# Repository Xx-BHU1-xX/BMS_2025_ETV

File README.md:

## Project archive for the 2025 ETV BMS
- Refer to the `hardware` section for design choices and PCB files.
- Refer to the `software` section for firmware dev.

## Yet to be implemented:
- Charging control and charger CAN comms
	- Control charging current and voltage according to INR1650 charge specs
	- J1939 CAN implementation for commanding charging current and voltage 
	- Should be relatively straightforard to implement with new task
- Inital SOH estimation
	- Detailed in the task description for `TaskUpdateSOC` 
- DCIR history
	- Store DCIR values in EEPROM for recovery in the next power cycle

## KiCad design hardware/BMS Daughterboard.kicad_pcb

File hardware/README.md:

# Battery Management System (BMS)

---

## Architecture evolution

### Earlier version
- Used **LTC6804-based slave boards (DC1894B)** with a **Linduino (DC2026)** as the isoSPI master.
- The entire system ran on the **ATmega328P** on the DC2026.
- SRAM was very limited (~2 KB), which was barely enough for:
  - 72× cell voltages, SOC, DCIR values
  - filtering / fault flags
- This became the main bottleneck as features were added.

---

### Revised architecture
- High-level processing was offloaded to an **ESP32**.
- The **DC2026** was retained only for reliable LTC6804 isoSPI communication.
- Direct isoSPI from the ESP32 was avoided to keep hardware and isolation simpler (and to avoid porting the LTC sketchbook :)

---

## Communication and isolation
- **ESP32** is referenced to **GLV**.
- **Linduino (DC2026)** is referenced to **TS**.
- Communication between the two is via an **isolated UART**.

---

## Additional features
- CAN communication for vehicle integration.
- Redundant isolated current sensing:
  - Hall-effect sensor (HBO300 fully differential)
  - Shunt-based sensor (VAT4300 wireless)

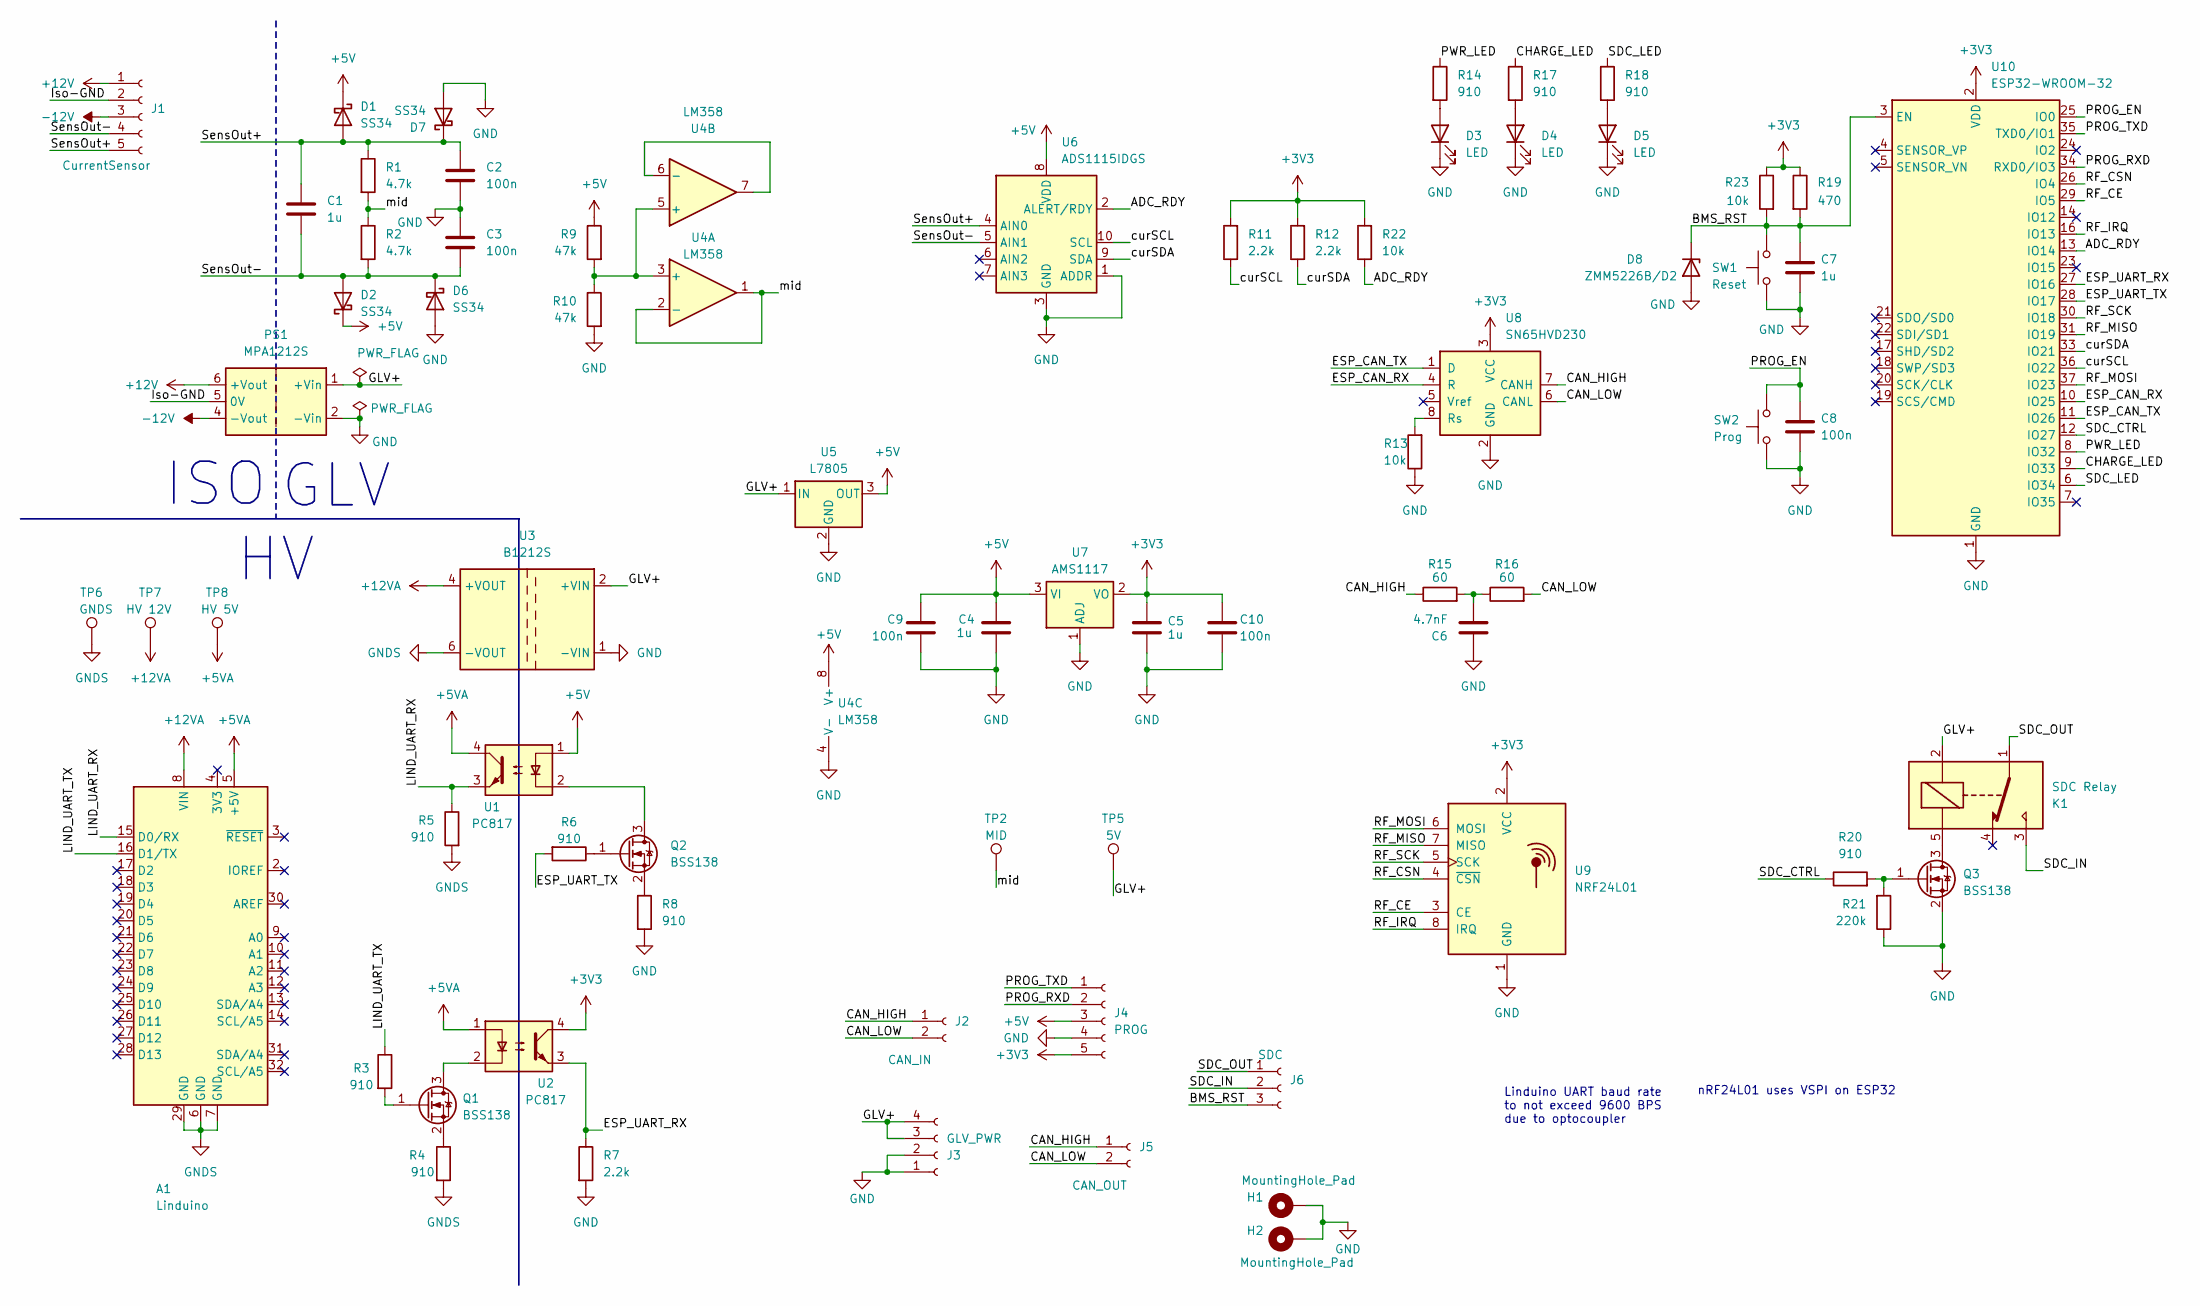
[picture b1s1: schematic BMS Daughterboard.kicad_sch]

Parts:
A1: Linduino
C1, C4, C5, C7: 1u; C_0805_2012Metric_Pad1.18x1.45mm_HandSolder
C2, C3, C8, C9, C10: 100n; C_0805_2012Metric_Pad1.18x1.45mm_HandSolder
C6: 4.7nF; C_0805_2012Metric_Pad1.18x1.45mm_HandSolder
D1, D2, D6, D7: SS34; D_SMC
D3, D4, D5: LED; LED_0805_2012Metric_Pad1.15x1.40mm_HandSolder
D8: ZMM5226B/D2; D_MiniMELF
H1, H2: MountingHole_Pad; MountingHole_3.2mm_M3_DIN965_Pad
J1: CurrentSensor; JST_PH_S5B-PH-K_1x05_P2.00mm_Horizontal
J2: CAN_IN; JST_PH_S2B-PH-K_1x02_P2.00mm_Horizontal
J3: GLV_PWR; JST_PH_S4B-PH-K_1x04_P2.00mm_Horizontal
J4: PROG; PinSocket_1x05_P2.54mm_Vertical
J5: CAN_OUT; JST_PH_S2B-PH-K_1x02_P2.00mm_Horizontal
J6: SDC; JST_PH_S3B-PH-K_1x03_P2.00mm_Horizontal
K1: SDC Relay; Relay_SPDT_SANYOU_SRD_Series_Form_C
PS1: MPA1212S; Converter_DCDC_XP_POWER-IAxxxxS_THT
Q1, Q2, Q3: BSS138
R1, R2: 4.7k; R_0805_2012Metric_Pad1.20x1.40mm_HandSolder
R3, R4, R5, R6, R8, R14, R17, R18, R20: 910; R_0805_2012Metric_Pad1.20x1.40mm_HandSolder
R7, R11, R12: 2.2k; R_0805_2012Metric_Pad1.20x1.40mm_HandSolder
R9, R10: 47k; R_0805_2012Metric_Pad1.20x1.40mm_HandSolder
R13, R22, R23: 10k; R_0805_2012Metric_Pad1.20x1.40mm_HandSolder
R15, R16: 60; R_0805_2012Metric_Pad1.20x1.40mm_HandSolder
R19: 470; R_0805_2012Metric_Pad1.20x1.40mm_HandSolder
R21: 220k; R_0805_2012Metric_Pad1.20x1.40mm_HandSolder
SW1: Reset; Push Button
SW2: Prog; Push Button
TP2: MID; TestPoint_Pad_D1.5mm
TP5: 5V; TestPoint_THTPad_D1.5mm_Drill0.7mm
TP6: GNDS; TestPoint_THTPad_D1.5mm_Drill0.7mm
TP7: HV 12V; TestPoint_THTPad_D1.5mm_Drill0.7mm
TP8: HV 5V; TestPoint_THTPad_D1.5mm_Drill0.7mm
U1, U2: PC817
U3: B1212S; DCDC B1212S
U4: LM358; SOIC-8_3.9x4.9mm_P1.27mm
U5: L7805; TO-252-2
U6: ADS1115IDGS; VSSOP-10_3x3mm_P0.5mm
U7: AMS1117; SOT-223-3_TabPin2
U8: SN65HVD230; SOIC-8_3.9x4.9mm_P1.27mm
U9: NRF24L01; nRF24L01_Breakout
U10: ESP32-WROOM-32

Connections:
+3V3: C5.1, C10.1, J4.5, R11.2, R12.2, R19.1, R22.2, R23.1, U2.4, U7.2 (VO), U8.3 (VCC), U9.2 (VCC), U10.2 (VDD)
+5V: C4.1, C9.1, D1.1 (K), D2.1 (K), J4.3, R9.1, U1.1, U4.8 (V+), U5.3 (OUT), U6.8 (VDD), U7.3 (VI)
+5VA: A1.5 (+5V), TP8.1, U1.4, U2.1
+12V: J1.1, PS1.6 (+Vout)
+12VA: A1.8 (VIN), TP7.1, U3.4 (+VOUT)
-12V: J1.3, PS1.4 (-Vout)
/ADC_RDY: R22.1, U6.2 (ALERT/RDY), U10.13 (IO14)
/BMS_RST: C7.1, D8.1 (K), J6.3, R19.2, R23.2, SW1.2, U10.3 (EN)
/CAN_HIGH: J2.1, J5.1, R15.1, U8.7 (CANH)
/CAN_LOW: J2.2, J5.2, R16.2, U8.6 (CANL)
/CHARGE_LED: R17.1, U10.9 (IO33)
/ESP_CAN_RX: U8.4 (R), U10.10 (IO25)
/ESP_CAN_TX: U8.1 (D), U10.11 (IO26)
/ESP_UART_RX: R7.1, U2.3, U10.27 (IO16)
/ESP_UART_TX: R6.2, U10.28 (IO17)
/GLV+: J3.3, J3.4, K1.2, PS1.1 (+Vin), TP5.1, U3.2 (+VIN), U5.1 (IN)
/Iso-GND: J1.2, PS1.5 (0V)
/LIND_UART_RX: A1.15 (D0/RX), R5.1, U1.3
/LIND_UART_TX: A1.16 (D1/TX), R3.1
/PROG_EN: C8.1, SW2.2, U10.25 (IO0)
/PROG_RXD: J4.2, U10.34 (RXD0/IO3)
/PROG_TXD: J4.1, U10.35 (TXD0/IO1)
/PWR_LED: R14.1, U10.8 (IO32)
/RF_CE: U9.3 (CE), U10.29 (IO5)
/RF_CSN: U9.4 (~CSN), U10.26 (IO4)
/RF_IRQ: U9.8 (IRQ), U10.16 (IO13)
/RF_MISO: U9.7 (MISO), U10.31 (IO19)
/RF_MOSI: U9.6 (MOSI), U10.37 (IO23)
/RF_SCK: U9.5 (SCK), U10.30 (IO18)
/SDC_CTRL: R20.1, U10.12 (IO27)
/SDC_IN: J6.2, K1.3
/SDC_LED: R18.1, U10.6 (IO34)
/SDC_OUT: J6.1, K1.1
/SensOut+: C1.1, C2.1, D1.2 (A), D7.1 (K), J1.5, R1.1, U6.4 (AIN0)
/SensOut-: C1.2, C3.2, D2.2 (A), D6.1 (K), J1.4, R2.2, U6.5 (AIN1)
/curSCL: R11.1, U6.10 (SCL), U10.36 (IO22)
/curSDA: R12.1, U6.9 (SDA), U10.33 (IO21)
/mid: R1.2, R2.1, TP2.1, U4.1, U4.2 (-)
GND: C2.2, C3.1, C4.2, C5.2, C6.1, C7.2, C8.2, C9.2, C10.2, D3.1 (K), D4.1 (K), D5.1 (K), D6.2 (A), D7.2 (A), D8.2 (A), H1.1, H2.1, J3.1, J3.2, J4.4, PS1.2 (-Vin), Q3.2 (S), R7.2, R8.2, R10.2, R13.1, R21.1, SW1.1, SW2.1, U3.1 (-VIN), U4.4 (V-), U5.2 (GND), U6.1 (ADDR), U6.3 (GND), U7.1 (ADJ), U8.2 (GND), U9.1 (GND), U10.1 (GND), U10.15 (GND), U10.38 (GND), U10.39 (GND)
GNDS: A1.6 (GND), A1.7 (GND), A1.29 (GND), R4.2, R5.2, TP6.1, U3.6 (-VOUT)
unnamed: C6.2, R15.2, R16.1
unnamed: D3.2 (A), R14.2
unnamed: D4.2 (A), R17.2
unnamed: D5.2 (A), R18.2
unnamed: Q1.3 (D), U2.2
unnamed: Q1.1 (G), R3.2
unnamed: Q1.2 (S), R4.1
unnamed: Q2.3 (D), U1.2
unnamed: Q2.1 (G), R6.1
unnamed: Q2.2 (S), R8.1
unnamed: K1.5, Q3.3 (D)
unnamed: Q3.1 (G), R20.2, R21.2
unnamed: R9.2, R10.1, U4.3 (+), U4.5 (+)
unnamed: U4.6 (-), U4.7
unnamed: R13.2, U8.8 (Rs)

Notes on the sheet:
GLV
nRF24L01 uses VSPI on ESP32
Linduino UART baud rate to not exceed 9600 BPS due to optocoupler
ISO

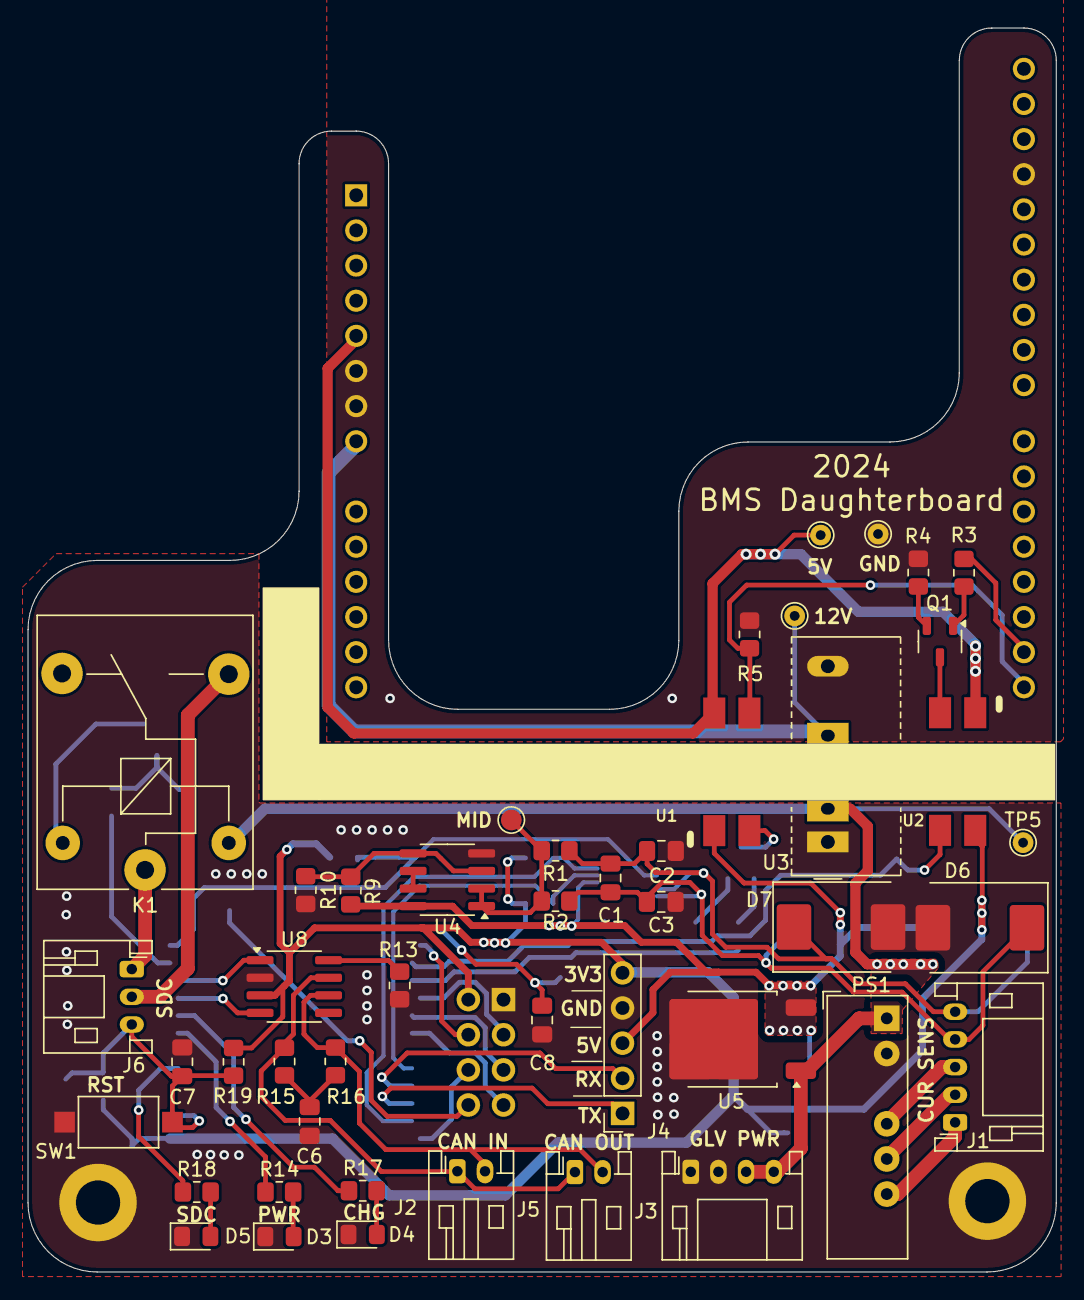
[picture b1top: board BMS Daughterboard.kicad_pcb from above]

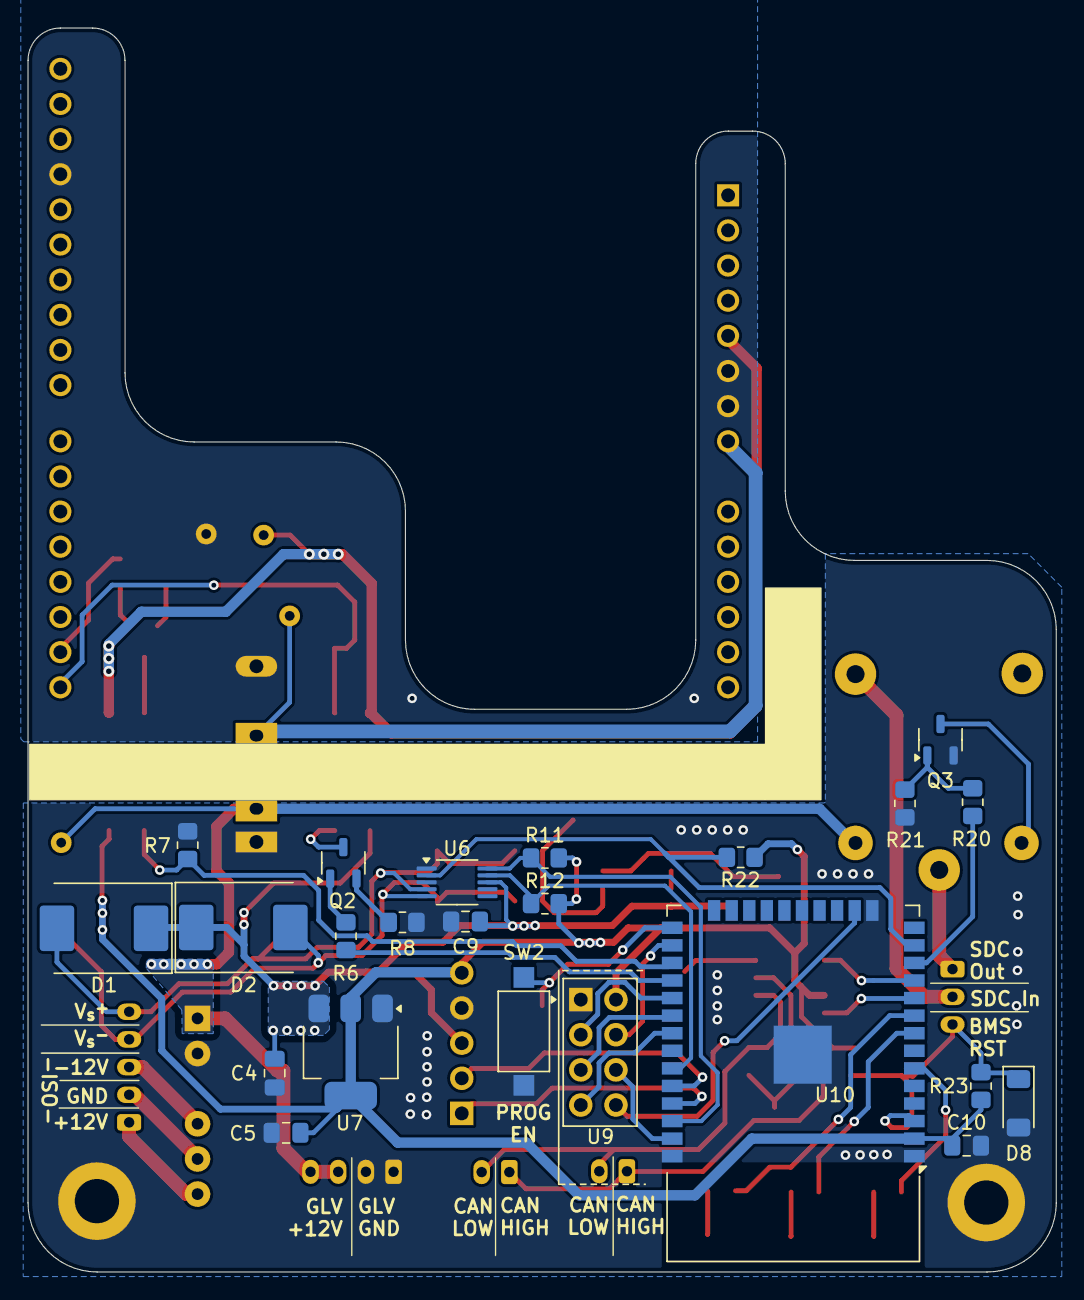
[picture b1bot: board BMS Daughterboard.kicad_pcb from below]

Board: 2 copper layers, 74.3 x 89.9 mm, 72 parts (23 on the bottom side), 55 nets.

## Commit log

2025-12-26 changed image
2025-12-26 changed image path
2025-12-26 PCB files
2025-12-26 adding readme
2025-12-26 adding software
2025-12-26 removing build
2025-12-27 formatted hardware README
2025-12-27 moving
2025-12-27 new dir
2025-12-27 correction
2025-12-27 added README with PCB pictures
2025-12-27 Added PCB pictures
2025-12-27 changed README pic path
2026-01-13 adding docs and README
2026-01-13 adding project home README
2026-01-13 chnaged project README
2026-01-13 added remaining tasks to project README
